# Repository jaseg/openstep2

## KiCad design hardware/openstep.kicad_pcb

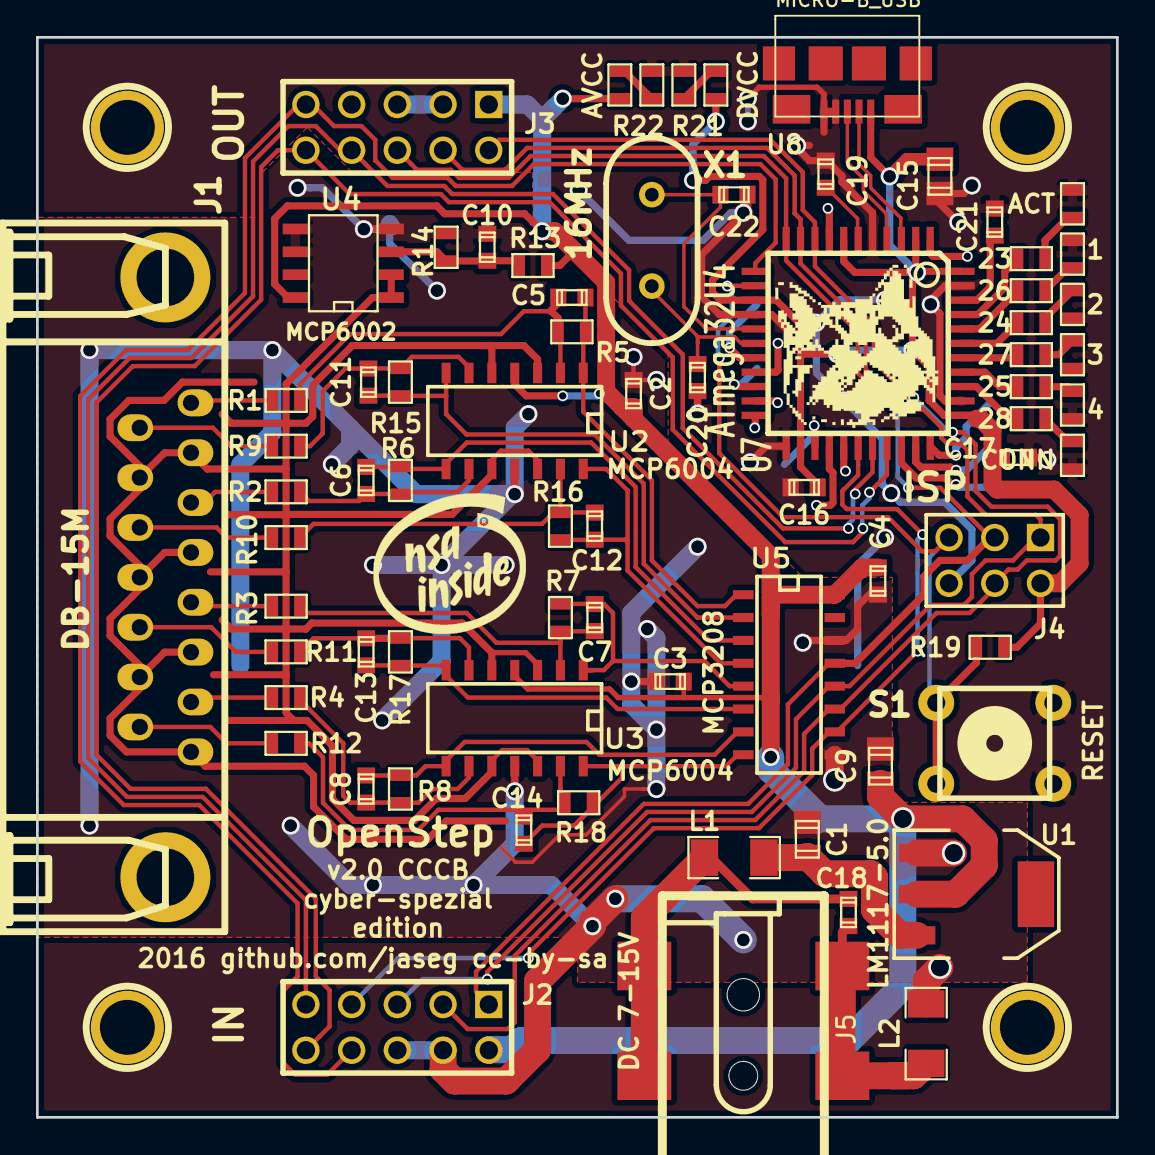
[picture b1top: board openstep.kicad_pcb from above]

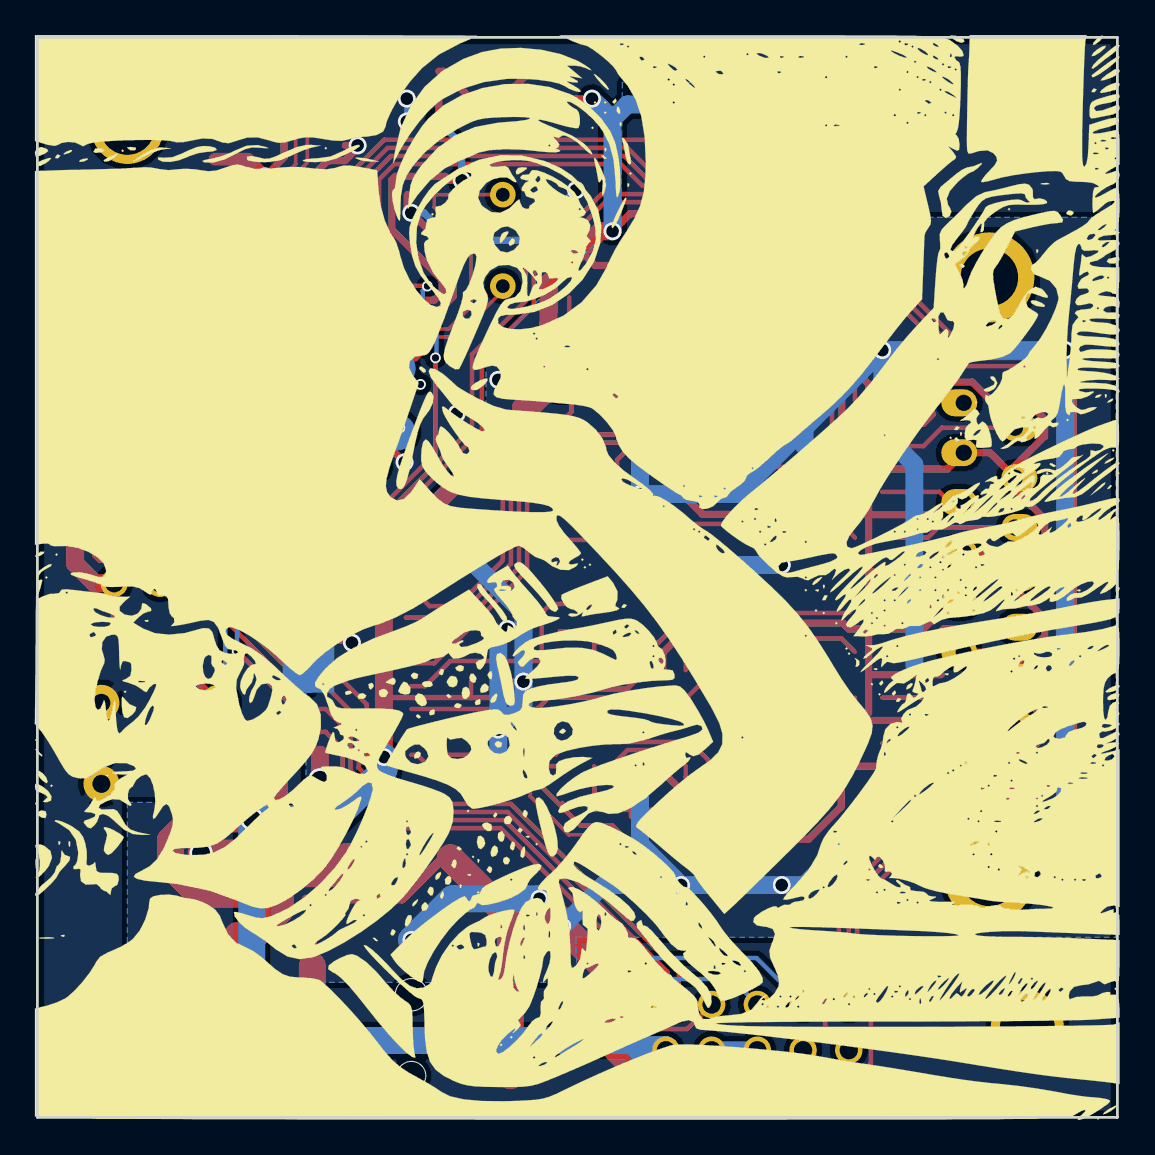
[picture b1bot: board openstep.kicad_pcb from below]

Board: 2 copper layers, 60.0 x 60.0 mm, 91 parts (14 on the bottom side), 74 nets.

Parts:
1: CH24-32; SM0603
1PIN, 1PIN#2, 1PIN#3, 1PIN#4: P***; 1pin
2: CH16-13; SM0603
3: CH8-15; SM0603
4: CH0-7; SM0603
23, 24, 25, 26, 27, 28: 220; SM0603
ACT: ACT; SM0603
AVCC: AVDD; SM0603
C1, C9, C15: 10u; c_0805
C2, C3, C4, C16, C17, C21: 100n; c_0603
C5, C6, C7, C8, C11, C12, C13, C14: C_; c_0603
C10: 1n; c_0603
C18: 100p; c_0603
C19: 1u; c_0603
C20, C22: 22p; c_0603
CONN: CONN; SM0603
DVCC: DVDD; SM0603
J1: DB-15M; DB_15M
J2: Chain IN; PIN_ARRAY_5x2
J3: Chain OUT; PIN_ARRAY_5x2
J4: AVRISP; pin_array_3x2
J5: BARREL_JACK; LUMBERG_1613_14
L1, L2: INDUCTOR_SMALL; SM1206
P1, P2, P3, P4, P5, P6, P7, P8, P9, P10, P11, P12, P13: CONN_1; TP_OPENSTEP
R1, R2, R3, R4, R5, R6, R7, R8, R9, R10, R11, R12, R15, R16, R17, R18, R19: R_; SM0603
R13, R14: 470k; SM0603
R20: 0R; NETTIE
R21, R22: 220; SM0603
S1: SW6x6; PCB_PUSH
U1: LM1117-5.0; SOT223
U2, U3: MCP6004; SO14E
U4: MCP6002; SO8E
U5: MCP3208; SO16E
U7: ATmega32U4; TQFP44
U8: MICRO-B_USB
X1: 16MHz; HC-49V

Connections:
+5VA: AVCC.1, C2.1, C3.1, C4.1, C9.1, J2.2, J3.1, R13.1, U1.2, U2.4, U3.4, U4.8, U5.16
+5VD: C15.1, C16.1, C17.1, DVCC.1, J4.2, R19.1, U7.2, U7.7, U7.14, U7.24, U7.34, U7.44, U8.1
/ADC_CS0: J2.7, U5.10, U7.28
/ADC_CS1: J2.9, J3.8, U7.29
/ADC_CS2: J2.10, J3.10, U7.30
/ADC_CS3: J2.8, J3.9, U7.12
/MISO: J2.5, J3.6, J4.1, U5.12, U7.11
/MOSI: J2.3, J3.4, J4.4, U5.11, U7.10
/SCK: J2.1, J3.2, J4.3, U5.13, U7.9
/V_IN: C1.1, L1.2, U1.3
/~RESET: J4.5, R19.2, S1.1, S1.4, U7.13
GND: 1.2, 2.2, 3.2, 4.2, ACT.2, C15.2, C16.2, C17.2, C19.2, C20.2, C21.2, C22.2, CONN.2, J4.6, R20.2, R21.1, R22.1, S1.2, S1.3, U7.5, U7.15, U7.23, U7.35, U7.43, U8.4, U8.5
GNDA: J1.2, J1.4, J1.6, J1.8, J1.10, J1.12, J1.14, U2.3, U2.5, U2.10, U2.12, U3.3, U3.5, U3.10, U3.12, U4.1, U4.2
unnamed: C5.1, R1.2, R5.1, U2.2
unnamed: C5.2, R5.2, U2.1, U5.1
unnamed: C6.1, R2.2, R6.1, U2.9
unnamed: C6.2, R6.2, U2.8, U5.3
unnamed: C7.1, R3.2, R7.1, U3.2
unnamed: C7.2, R7.2, U3.1, U5.5
unnamed: C8.1, R4.2, R8.1, U3.9
unnamed: C8.2, R8.2, U3.8, U5.7
unnamed: C10.1, R13.2, R14.1, U4.3
unnamed: C11.1, R9.2, R15.1, U2.6
unnamed: C11.2, R15.2, U2.7, U5.2
unnamed: C12.1, R10.2, R16.1, U2.13
unnamed: C12.2, R16.2, U2.14, U5.4
unnamed: C13.1, R11.2, R17.1, U3.6
unnamed: C13.2, R17.2, U3.7, U5.6
unnamed: C14.1, R12.2, R18.1, U3.13
unnamed: C14.2, R18.2, U3.14, U5.8
unnamed: C18.1, J5.1, L1.1
unnamed: C18.2, J5.2, J5.3, L2.1
unnamed: C19.1, U7.6
unnamed: C20.1, U7.17, X1.1
unnamed: C21.1, U7.42
unnamed: C22.1, U7.16, X1.2
unnamed: DVCC.2, R21.2
unnamed: 26.2, ACT.1
unnamed: 3.1, 27.2
unnamed: 1.1, 28.2
unnamed: AVCC.2, R22.2
unnamed: 23.2, CONN.1
unnamed: 4.1, 24.2
unnamed: 2.1, 25.2
unnamed: J1.1, R1.1
unnamed: J1.3, R2.1
unnamed: J1.5, R3.1
unnamed: J1.7, R4.1
unnamed: J1.9, R9.1
unnamed: J1.11, R10.1
unnamed: J1.13, R11.1
unnamed: J1.15, R12.1
unnamed: P1.1, U7.31
unnamed: P2.1, U7.32
unnamed: P3.1, U7.18
unnamed: P4.1, U7.19
unnamed: P5.1, U7.20
unnamed: P6.1, U7.21
unnamed: P7.1, U7.25
unnamed: P8.1, U7.22
unnamed: P9.1, U7.26
unnamed: P10.1, U7.27
unnamed: P11.1, U7.33
unnamed: P12.1, U7.1
unnamed: P13.1, U7.8
unnamed: 23.1, U7.41
unnamed: 24.1, U7.39
unnamed: 25.1, U7.37
unnamed: 26.1, U7.40
unnamed: 27.1, U7.38
unnamed: 28.1, U7.36
unnamed: U7.3, U8.2
unnamed: U7.4, U8.3
VSS: C1.2, C2.2, C3.2, C4.2, C9.2, C10.2, J2.4, J2.6, J3.3, J3.5, L2.2, R14.2, R20.1, U1.1, U2.11, U3.11, U4.4, U4.5, U4.6, U5.9, U5.14

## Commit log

2016-05-15 Firmware: Fix ADC half
2016-05-15 Add slow matplotlib plotter
2016-05-15 plot faster
2016-05-16 make gui thing fancier
2016-06-27 hardware: initial board revision
2016-06-28 second board revision, fixed power supply stuff
2016-06-28 fixed chain conn orientation
2016-06-29 Add some more testpads for the CPU
2016-06-29 Prettified AVCC routing a bit
2016-06-29 Minor layout tweaks
2017-05-17 Release v2.0
2017-05-24 Gerber export, add BOM
2017-05-24 Add paste gerbers
2017-05-24 BOM: Add missing stuff
2017-05-30 BOM update

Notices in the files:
hardware/openstep.kicad_pcb:
2016 github.com/jaseg cc-by-sa
